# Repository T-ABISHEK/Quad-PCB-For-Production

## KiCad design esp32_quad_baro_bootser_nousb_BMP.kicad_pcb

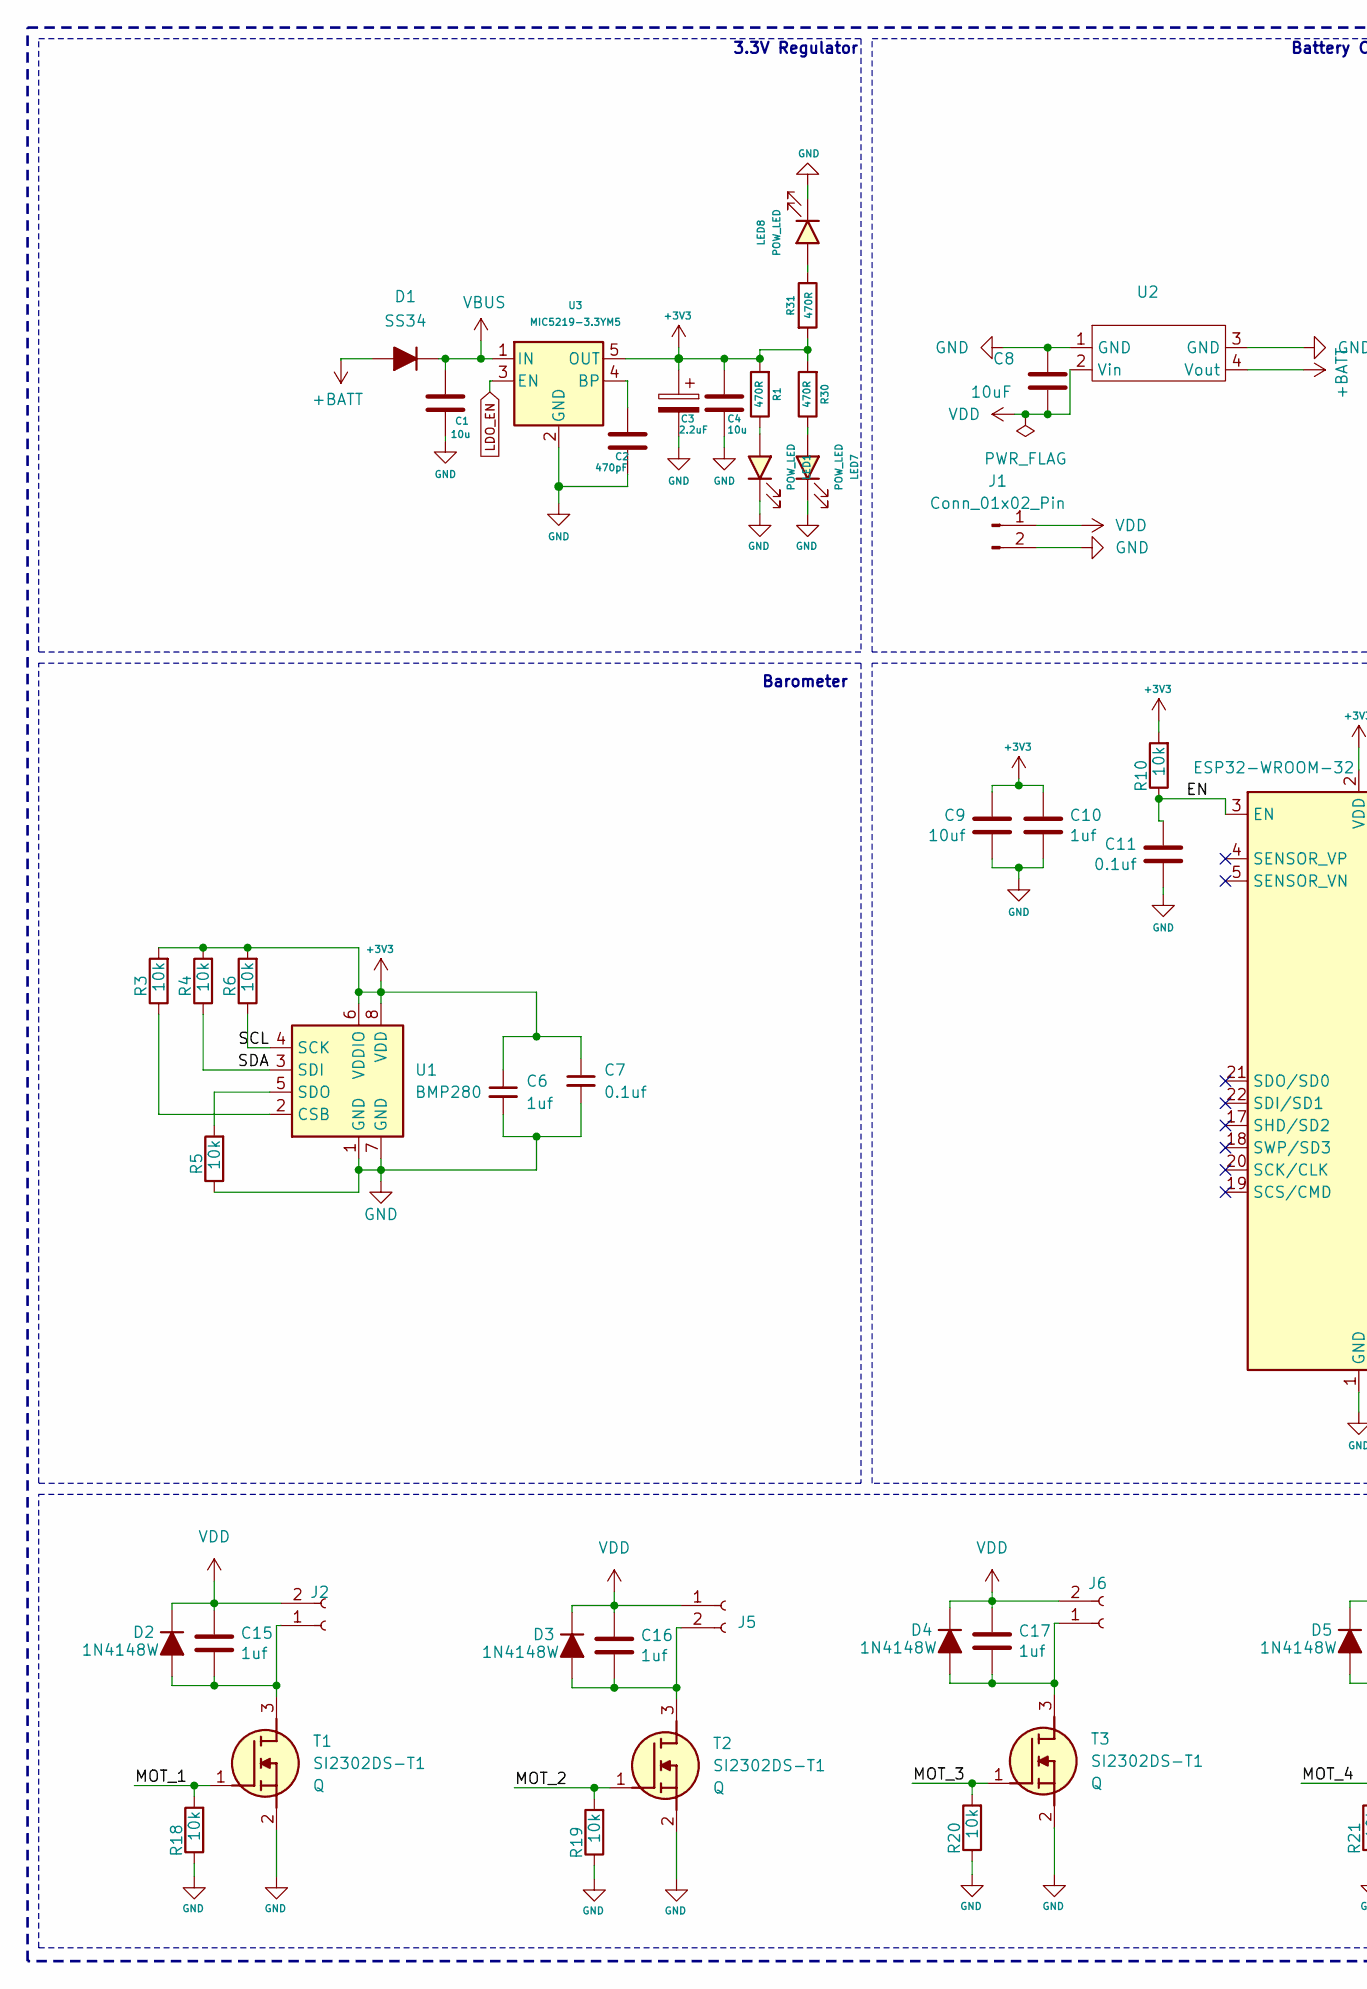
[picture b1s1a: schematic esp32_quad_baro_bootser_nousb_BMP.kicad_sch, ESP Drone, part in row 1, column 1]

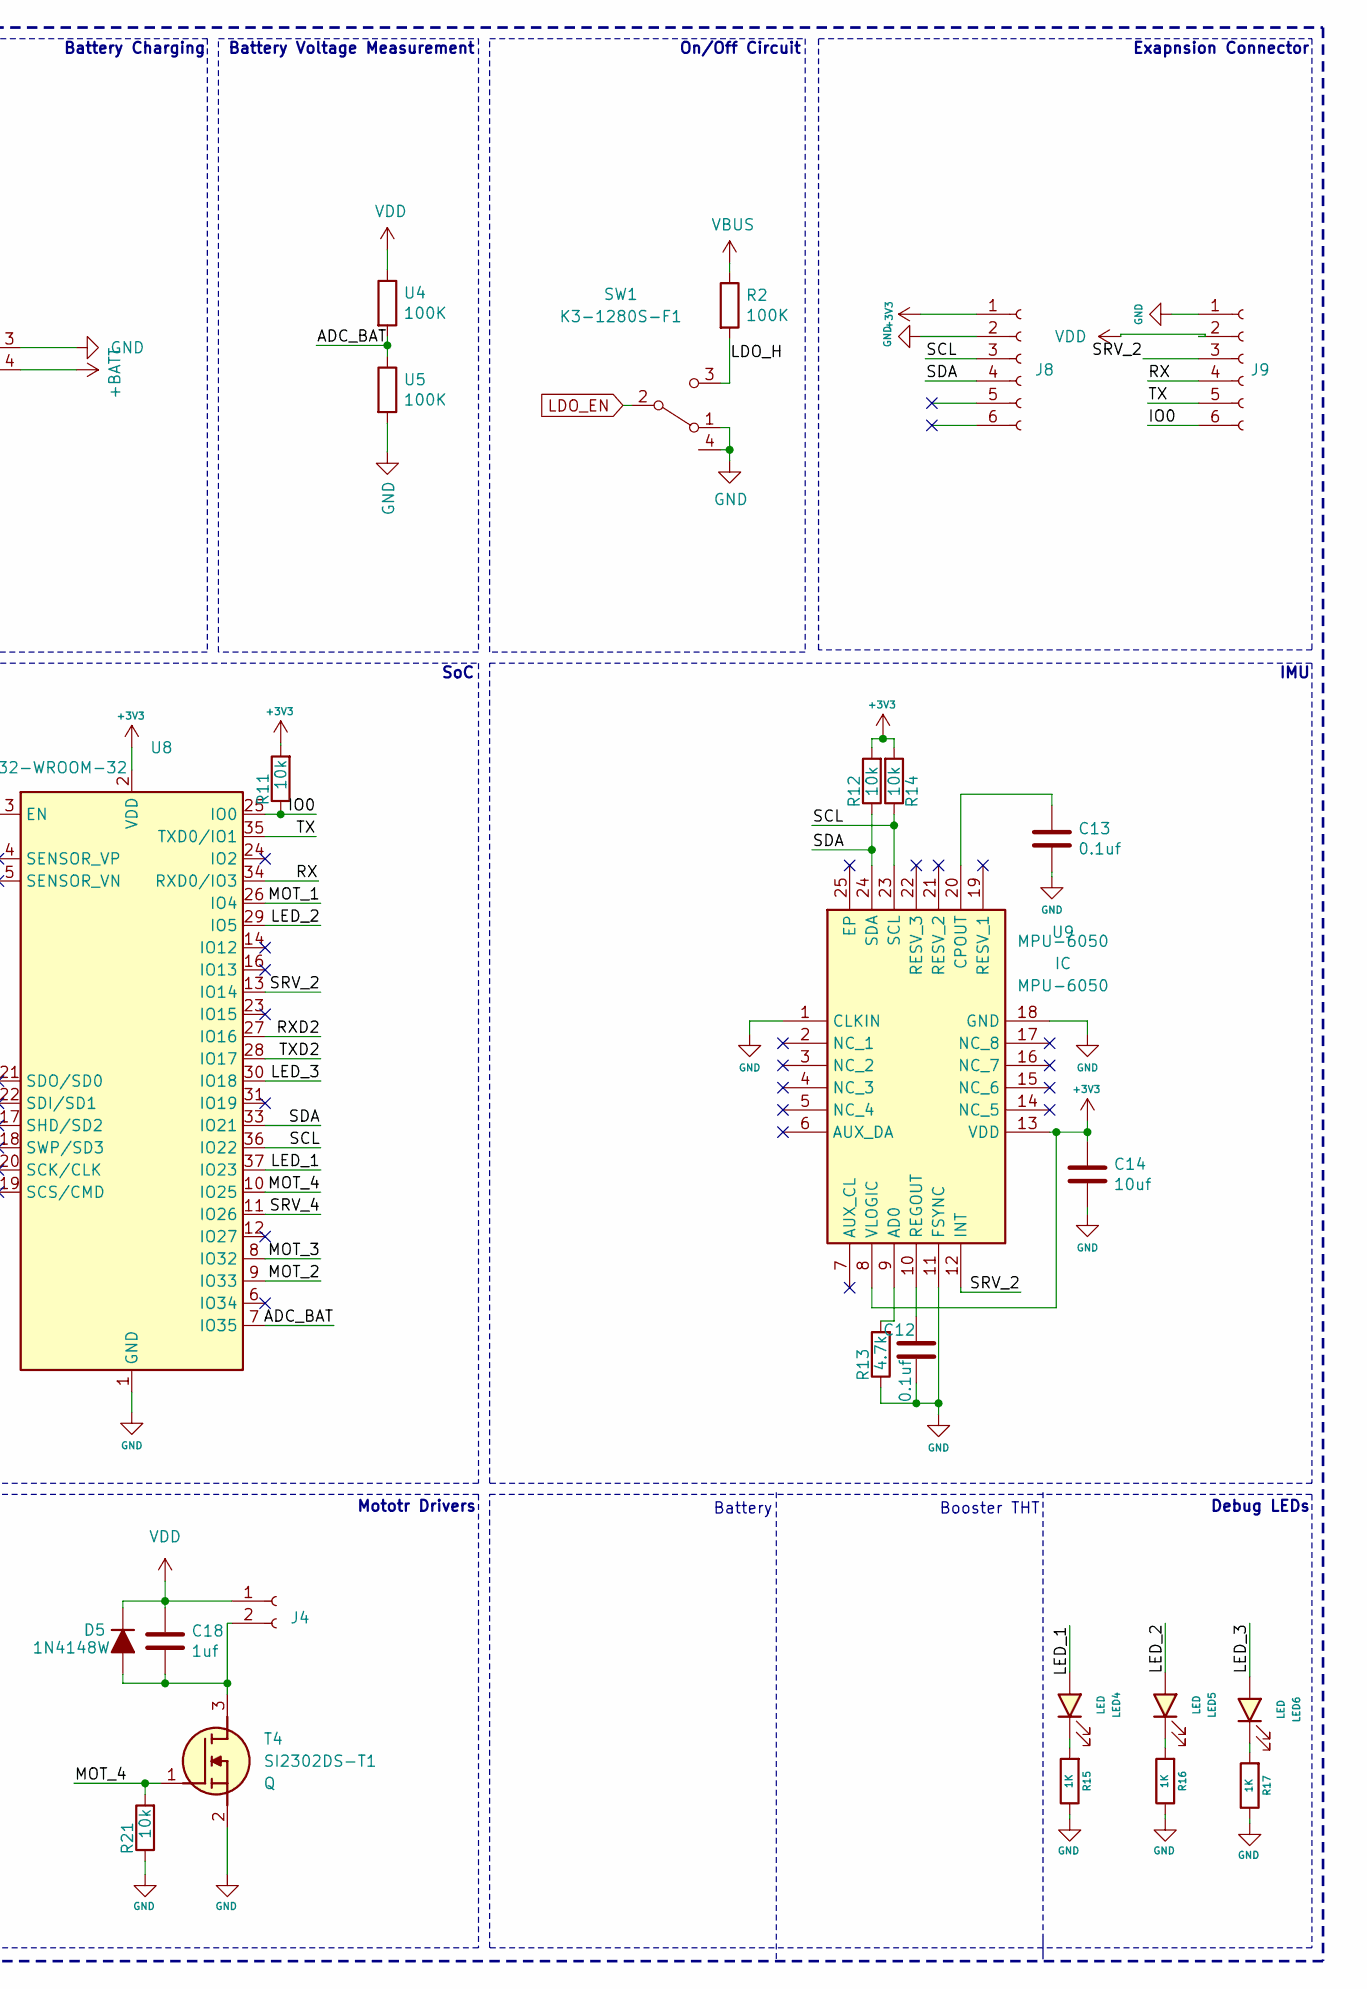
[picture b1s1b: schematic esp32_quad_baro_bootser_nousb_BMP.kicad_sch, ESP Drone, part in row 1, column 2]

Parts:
C1, C4: 10u; C_0603_1608Metric
C2: 470pF; C_0603_1608Metric
C3: 2.2uF; C_0805_2012Metric
C6, C10, C15, C16, C17, C18: 1uf; C_0603_1608Metric
C7, C11, C12, C13: 0.1uf; C_0603_1608Metric
C8: 10uF; C_0603_1608Metric
C9, C14: 10uf; C_0603_1608Metric
D1: SS34; D_SMA
D2, D3, D4, D5: 1N4148W; D_SOD-323
J1: Conn_01x02_Pin; Molex_Micro-Latch_53253-0270_1x02_P2.00mm_Vertical
J2, J4, J5, J6: Conn_01x02_Female; Hirose_DF13-02P-1.25DSA_1x02_P1.25mm_Vertical
J8, J9: Conn_01x06_Female; PinHeader_1x06_P2.54mm_Vertical
LED1, LED7, LED8: POW_LED; LED_0603_1608Metric
LED4, LED5, LED6: LED; LED_0603_1608Metric
R1, R30, R31: 470R; R_0603_1608Metric
R2: 100K; R_0603_1608Metric
R3, R4, R5, R6, R10, R11, R12, R14, R18, R19, R20, R21: 10k; R_0603_1608Metric
R13: 4.7k; R_0603_1608Metric
R15, R16, R17: 1K; R_0603_1608Metric
SW1: K3-1280S-F1; SW-SMD_MSK-03-HB
T1, T2, T3, T4: SI2302DS-T1; SOT95P240X115-3N; Mouser Part Number 781-SI2302DS
U1: BMP280; Bosch_LGA-8_2x2.5mm_P0.65mm_ClockwisePinNumbering
U2: BS01
U3: MIC5219-3.3YM5; SOT-23-5
U4, U5: 100K; R_0603_1608Metric
U8: ESP32-WROOM-32
U9: MPU-6050; mpu6050; Mouser Part Number 410-MPU-6050

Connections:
+3V3: C3.1, C4.1, C6.1, C7.1, C9.1, C10.1, C14.1, J8.1, R1.2, R3.2, R4.2, R6.2, R10.2, R11.2, R12.2, R14.2, R30.2, R31.2, U1.6 (VDDIO), U1.8 (VDD), U3.5 (OUT), U8.2 (VDD), U9.8 (VLOGIC), U9.13 (VDD)
+BATT: D1.2 (A), U2.4 (Vout)
/ADC_BAT: U4.2, U5.1, U8.7 (IO35)
/EN: C11.1, R10.1, U8.3 (EN)
/IO0: J9.6, R11.1, U8.25 (IO0)
/LDO_H: R2.2, SW1.3 (C)
/LED_1: LED4.2 (A), U8.37 (IO23)
/LED_2: LED5.2 (A), U8.29 (IO5)
/LED_3: LED6.2 (A), U8.30 (IO18)
/MOT_1: R18.2, T1.1 (G), U8.26 (IO4)
/MOT_2: R19.2, T2.1 (G), U8.9 (IO33)
/MOT_3: R20.2, T3.1 (G), U8.8 (IO32)
/MOT_4: R21.2, T4.1 (G), U8.10 (IO25)
/RX: J9.4, U8.34 (RXD0/IO3)
/RXD2: U8.27 (IO16)
/SCL: J8.3, R6.1, R14.1, U1.4 (SCK), U8.36 (IO22), U9.23 (SCL)
/SDA: J8.4, R4.1, R12.1, U1.3 (SDI), U8.33 (IO21), U9.24 (SDA)
/SRV_2: J9.3, U8.13 (IO14), U9.12 (INT)
/SRV_4: U8.11 (IO26)
/TX: J9.5, U8.35 (TXD0/IO1)
/TXD2: U8.28 (IO17)
GND: C1.2, C2.2, C3.2, C4.2, C6.2, C7.2, C8.1, C9.2, C10.2, C11.2, C12.2, C13.2, C14.2, J1.2, J8.2, J9.1, LED1.1 (K), LED7.1 (K), LED8.1 (K), R5.1, R13.1, R15.1, R16.1, R17.1, R18.1, R19.1, R20.1, R21.1, SW1.1 (A), SW1.4, T1.2 (S), T2.2 (S), T3.2 (S), T4.2 (S), U1.1 (GND), U1.7 (GND), U2.1 (GND), U2.3 (GND), U3.2 (GND), U5.2, U8.1 (GND), U8.15 (GND), U8.38 (GND), U8.39 (GND), U9.1 (CLKIN), U9.11 (FSYNC), U9.18 (GND)
LDO_EN: SW1.2 (B), U3.3 (EN)
unnamed: C15.2, D2.2 (A), J2.1, T1.3 (D)
unnamed: C16.2, D3.2 (A), J5.2, T2.3 (D)
unnamed: C17.2, D4.2 (A), J6.1, T3.3 (D)
unnamed: C18.2, D5.2 (A), J4.2, T4.3 (D)
unnamed: LED1.2 (A), R1.1
unnamed: LED4.1 (K), R15.2
unnamed: LED5.1 (K), R16.2
unnamed: LED6.1 (K), R17.2
unnamed: LED7.2 (A), R30.1
unnamed: LED8.2 (A), R31.1
unnamed: R3.1, U1.2 (CSB)
unnamed: R5.2, U1.5 (SDO)
unnamed: C2.1, U3.4 (BP)
unnamed: R13.2, U9.9 (AD0)
unnamed: C13.1, U9.20 (CPOUT)
unnamed: C12.1, U9.10 (REGOUT)
VBUS: C1.1, D1.1 (K), R2.1, U3.1 (IN)
VDD: C8.2, C15.1, C16.1, C17.1, C18.1, D2.1 (K), D3.1 (K), D4.1 (K), D5.1 (K), J1.1, J2.2, J4.1, J5.1, J6.2, J9.2, U2.2 (Vin), U4.1

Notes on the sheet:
Booster THT
SoC
Battery Voltage Measurement
Battery
IMU
Mototr Drivers
Battery Charging
Debug LEDs
Exapnsion Connector
3.3V Regulator
On/Off Circuit
Barometer

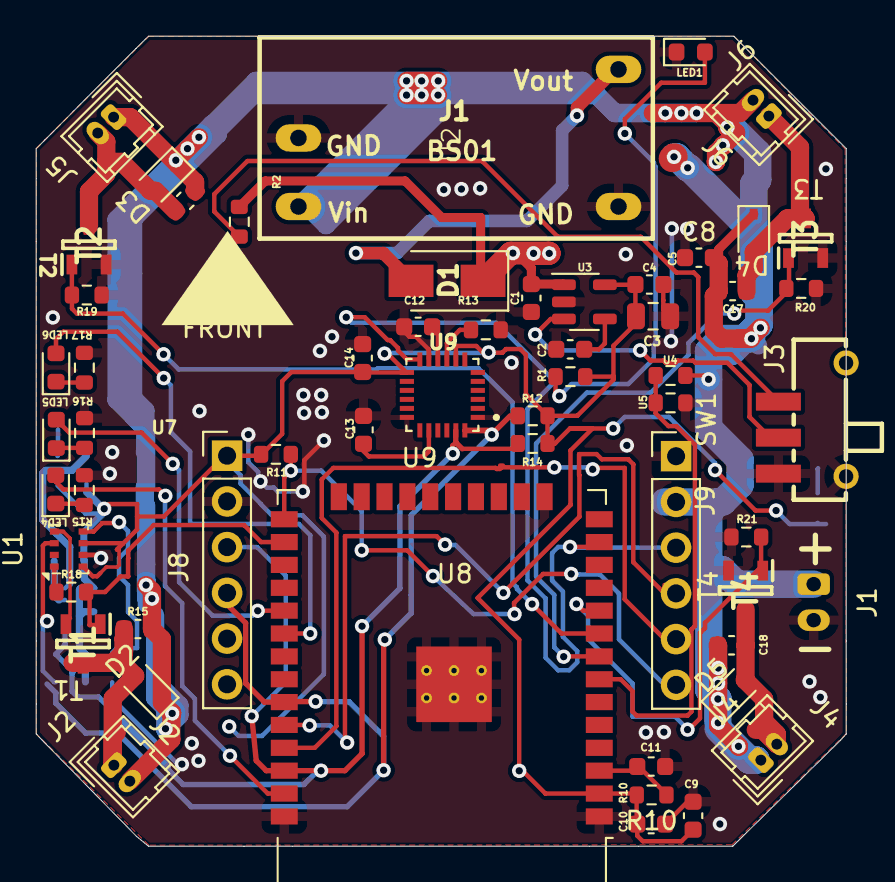
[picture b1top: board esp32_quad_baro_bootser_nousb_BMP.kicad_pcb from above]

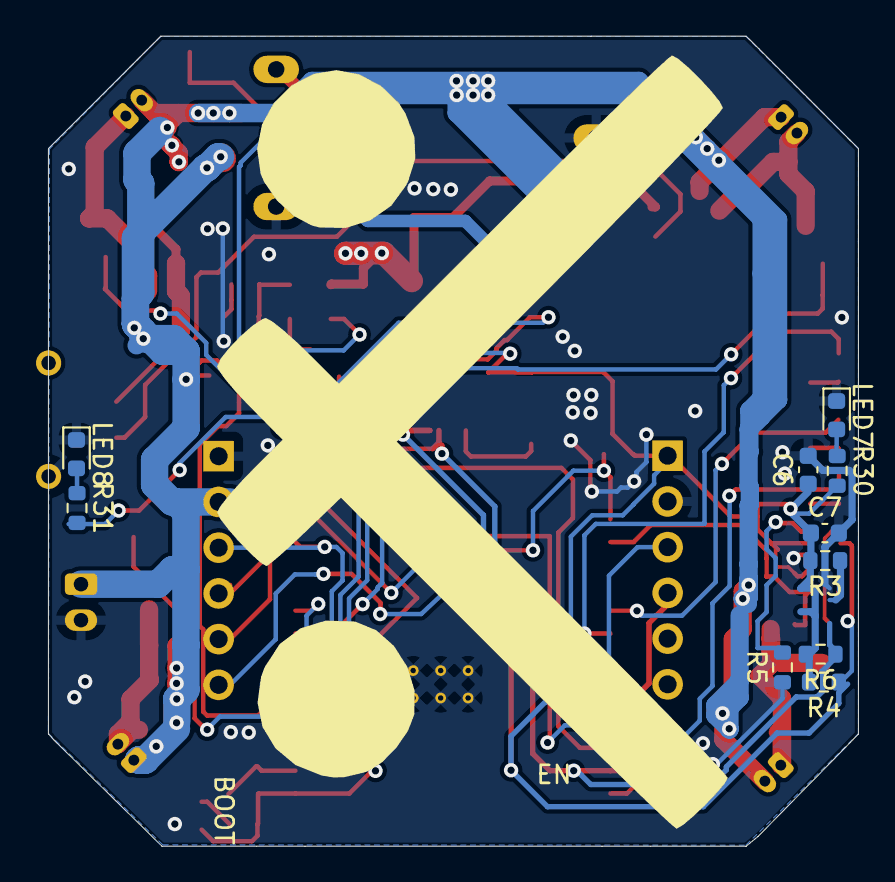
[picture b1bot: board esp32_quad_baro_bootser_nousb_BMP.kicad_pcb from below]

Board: 2 copper layers, 45.0 x 45.0 mm, 67 parts (10 on the bottom side), 38 nets.

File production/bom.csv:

Designator,Footprint,Quantity,Value,LCSC Part #
"C1, C4",0603,2,10u,
"C10, C15, C16, C17, C18, C6",0603,6,1uf,
"C11, C12, C13, C7",0603,4,0.1uf,
"C14, C8, C9",0603,3,10uf,
C2,0603,1,470pF,
C3,0805,1,2.2uF,
D1,D_SMA,1,SS34,
"D2, D3, D4, D5",D_SOD-323,4,1N4148W,
J1,Molex_Micro-Latch_53253-0270_1x02_P2.00mm_Vertical,1,Conn_01x02_Pin,
"J2, J4, J5, J6",Hirose_DF13-02P-1.25DSA_1x02_P1.25mm_Vertical,4,Conn_01x02_Female,
"J8, J9",PinHeader_1x06_P2.54mm_Vertical,2,Conn_01x06_Female,
"LED1, LED7, LED8",0603,3,POW_LED,
"LED4, LED5, LED6",0603,3,LED,
"R1, R30, R31",0603,3,470R,
"R10, R11, R12, R14, R18, R19, R20, R21, R3, R4, R5, R6",0603,12,10k,
R13,0603,1,4.7k,
"R15, R16, R17",0603,3,1K,
"R2, U4, U5",0603,3,100K,
SW1,SW-SMD_MSK-03-HB,1,K3-1280S-F1,
"T1, T2, T3, T4",SOT95P240X115-3N,4,SI2302DS-T1,
U1,Bosch_LGA-8_2x2.5mm_P0.65mm_ClockwisePinNumbering,1,BMP280,
U2,BS01,1,~,
U3,SOT-23-5,1,MIC5219-3.3YM5,
U8,ESP32-WROOM-32,1,ESP32-WROOM-32,
U9,mpu6050,1,MPU-6050,

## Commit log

2025-04-25 lite
2025-04-25 CHANGED WIRE THICKNESS
2025-04-25 PCB
    C:\Users\Robo\Downloads\New folder (2)\OUTPUT
2025-04-25 PCB1
    ALL FILE IS OK....? SEE BRO
